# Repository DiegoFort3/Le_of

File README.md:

View this project on [CADLAB.io](https://cadlab.io/project/27247). 

# Le_of

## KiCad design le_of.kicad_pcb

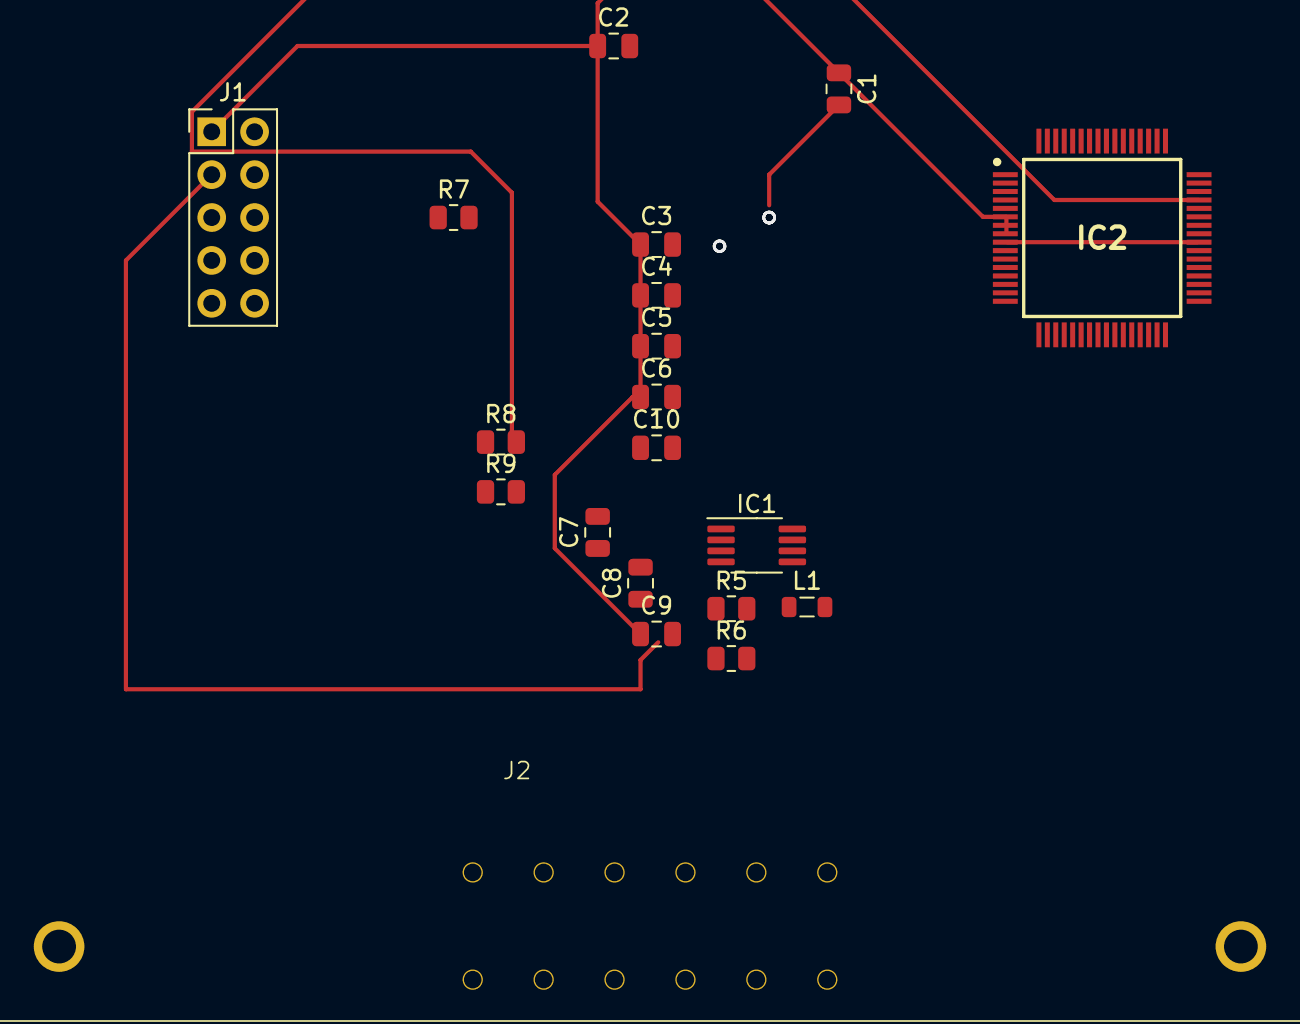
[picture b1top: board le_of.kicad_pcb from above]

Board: 4 copper layers, 20 parts (0 on the bottom side), 12 nets.

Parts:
C1, C2: 4u7; C_0805_2012Metric
C3, C4, C6, C10: 100n0; C_0805_2012Metric
C5, C8: 1u0; C_0805_2012Metric
C7: 22n0; C_0805_2012Metric
C9: 10u0; C_0805_2012Metric
IC1: LTC3631EMS8E-3.3#PBF; MSOP-8_3x3mm_P0.65mm
IC2: STM32G0B1RET6N; QFP50P1200X1200X160-64N
J1: ST_Link_Connector; PinHeader_2x05_P2.54mm_Vertical
J2: ATM13-12PA-R008
L1: 2u2; L_0805_2012Metric
R5: 294k0; R_0805_2012Metric
R6: 93k1; R_0805_2012Metric
R7, R8, R9: 20; R_0805_2012Metric

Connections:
+3V3: C1.1, C2.1, C3.1, C4.1, C5.1, C6.1, C9.1, IC2.6 (VBAT), IC2.7 (VREF+), IC2.8 (VDD/VDDA), IC2.41 (VDDIO2), J1.1, L1.2, R5.1
/NSRT: J1.10, R9.1
/Power_distribution/V_in: C8.1, IC1.2 (VIN), IC1.5 (RUN), J2.6
/SWCLK: J1.4, R7.1
/SWDIO: J1.2, R8.1
/microprocessor/NRST: C10.1, IC2.12 (PF2-NRST), R9.2
/microprocessor/SWCLK: IC2.46 (PA14-BOOT0), R7.2
/microprocessor/SWDIO: IC2.45 (PA13), R8.2
GND: C1.2, C2.2, C3.2, C4.2, C5.2, C6.2, C7.2, C8.2, C9.2, C10.2, IC1.8 (GND_1), IC2.9 (VSS/VSSA), IC2.40 (VSS), J1.3, J1.5, R6.2
unnamed: C7.1, IC1.3 (ISET), IC1.4 (SS)
unnamed: IC1.1 (SW), L1.1
unnamed: IC1.6 (VOUT/VFB), R5.2, R6.1

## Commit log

2023-08-11 Init commit
2023-08-12 Finished ST link
2023-08-12 Backlink to CADLAB.io has been added.
2023-08-14 Started adding footprints. Finished wiring up schematic
2023-08-14 added footrpints
2023-08-16 Added library. its in the overall kicad folder for me. Added footrpint for stuff
2023-08-16 Should have done a branch instead for this but oh well
2023-08-17 Added submodule
2023-08-18 Updated submodule
2023-09-01 added a whole lot of footprints and layout
2023-09-01 idk man
2023-09-01 last min save
2023-09-01 added bunch
2023-09-04 added net labels
2023-09-06 Init commit for laptop version
2023-09-06 made small changes
2023-09-06 small
